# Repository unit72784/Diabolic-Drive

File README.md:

# Diabolic Drive

# 💀 The final Diabolic Drive firmware is live — locked, loaded, and lethal.This isn’t just an update — it’s a full-scale upgrade built for offensive ops in the real world. Designed by UNIT 72784. One mind. Full control. For every hacker. You’ve waited long enough. Flash it. Wreck everything. Break what must be broken. 💀
# [New firmware installation instructions are here.](https://github.com/unit72784/Diabolic-Drive/blob/main/New%20firmware%20installation%20instructions.md)
<p align="center">
  <a href="https://www.youtube.com/watch?v=nSBRwmqkTx8">
    
    <br>
    <b>Watch Diabolic Drive Teaser</b>
  </a>
</p>

---

* [Firmware ChangeLog](#firmware-changelog)
* [Usage](#usage)
* [About](#about)
* [Why Diabolic Drive ?](#why-diabolic-drive-)
* [How Stealth can Diabolic Drive go ?](#how-stealth-can-diabolic-drive-go-)
* [Features](#features)
* [Flash Software](#flash-software)
  + [Flash Atmega32u4](#flash-atmega32u4)
  + [Flash ESP8266](#flash-esp8266)
* [Programming Options](#programming-options)
  + [ESP8266](#esp8266)
  + [ATMEGA32U4](#atmega32u4)
  + [Access ATMEGA32U4 Bootloader](#access-atmega32u4-bootloader)
* [Technical Specifications](#technical-specifications)
* [Credits](#credits)

<h1>:bangbang: Diabolic Drive default access point credentials are:
  <br>Wi-Fi SSID: DDv1</br>
  Password: diabolic_drive 
  :bangbang:
</h1>

# Firmware ChangeLog 
### 1. Dynamic Hardware ID Spoofing :
Spoof the VID and PID of your Diabolic Drive over the Web UI using the USBID command.

### 2. Side-Channel Exfiltration with Keystroke Reflection
Capture and reflect keystrokes in real-time for stealthy data extraction.

### 3. LangIgnore Mode
No layout? No problem. Payloads are delivered consistently using ALT + numpad ASCII codes, bypassing language settings across all keyboard layouts.

### 4. OS Detection
Automatically detects the target operating system so you can adapt payloads accordingly.

### 5. Configurable Random Typing Cadence
Human-like keystroke timing to avoid behavioral detection systems.

### 6. Revamped Web UI
Completely refreshed interface — cleaner, faster, and more intuitive than ever.

### 7. DNS Redirection with Captive Portal
ensures all requests go to the onboard web server, displaying a captive portal instead of a “no internet” message. On mobile devices, it eliminates the need to disable mobile data to access the web interface.

### 8. Stability & Performance
Tons of under-the-hood bug fixes, stability improvements, and overall performance boosts.

## Usage
1. Plug in your Diabolic Drive
2. <b>Connect to the WiFi network `DDv1` with the default password `diabolic_drive`</b>
3. Open the browser on the device you used to connect to your Diabolic Drive and visit `192.168.4.1` or `diabolic.drive`
4. Your Diabolic Drive comes preloaded with a test Ducky script, which I used in the testing phase to check if the Diabolic Drive key stroke injection works properly. No worries about it; it's just a powershell command that retrieves the credentials of the Diabolic Drive access point from your Windows machine if it's already saved and you have connected to it from your computer before.
5. To access `Settings` along with other menus, click on the 3 horizontal bars icon (top right corner).

<h3> <del>
‼️The software that comes preloaded with the already-shipped Diabolic Drive is in a very early beta phase (built on WiFiDuck) with some modifications to suit the Diabolic Drive and to integrate the Spectre POC feature just to get things up and running. After ensuring all Diabolic Drives are delivered to the backers, I will start working on the software side and adding features to it.‼️
</del>
  <br>
  <br>
✅ <strong>This is now complete. Final firmware is released.</strong>
  
<br>Feel free to subscribe to the <a href="https://www.youtube.com/@unit72784">UNIT 72784 YouTube channel</a>; many great videos, feature updates and use-case scenarios will be posted there very soon!</br>
</h3> 

## About

Diabolic Drive isn’t just another HID injector — it’s a full-blown offensive implant wrapped in the body of a perfectly normal 64GB flash drive.

Plug it in and it plays the part: real storage, clean profile, zero suspicion. But behind the scenes, it’s wirelessly waiting to strike — injecting keystrokes, executing payloads, and slipping past defenses in plain sight.

Built for red teamers, crafted for covert ops, and born for social engineering. This isn’t a bad USB — it’s the next generation.

---

## Why Diabolic Drive ?
What’s the one USB device people still trust enough to plug in without thinking? A flash drive. No cables. No adapters. Just something simple, familiar, and everywhere.

Think about it — when was the last time you plugged in a USB cable just for data? Now think about how often flash drives get used. Exactly.

But just looking like a flash drive isn’t enough anymore — people are catching on. So Diabolic Drive doesn’t just look legit — it is legit. A full 64GB of real, usable storage. No gimmicks. No dead shells. Plug it in, and it behaves exactly like a standard thumb drive.

That’s what makes it dangerous.

It blends in, earns trust, and delivers payloads with surgical precision. Whether you’re baiting targets in the wild or slipping it into a physical pentest, Diabolic Drive is built for the job — engineered for social engineering.

***Diabolic Drive on the left, standard flash drive on the right**

## How Stealth can Diabolic Drive go ?
**there are 4 main features that make Diabolic Drive very Stealth**
- **PCB design is in Universal Flash Drive PCB shape.** For any person with good security awareness, plugging in a generic-looking or very old-fashioned USB 2.0 flash drive might not be the best option to go for., This is why I decided to go with the trendy shapes of modern-looking USB 3.0 flash drives and the most common available models. I did lots of recon, got many models disassembled, identified the PCB dimensions, and finally managed to get a universal PCB shape that I needed to design my PCB identical to to help the Diabolic Drive be much more stealthy, hiding itself in many common USB 3.0 flash drive enclosures out there!
 **Disclaimer :  Enclosure in image below is for demonstration purposes only !**

- **plug in your Diabolic Drive to a USB port will raise only one USB plug in sound** When Diabolic Drive is plugged into a host computer, it acts just like a regular USB flash drive, including any audio notifications you would normally hear when plugging in a new USB device. Your computer will identify Diabolic Drive as a flash drive, HID device, and virtual COM port simultaneously <b>(Now with SPECTRE, your computer will only identify it as a flash drive, and the HID interface remains dormant until you fire your payload.)</b>, but will only trigger an audio notification once, which is how a standard drive would behave. 
<p align="center">
  <a href="https://www.youtube.com/watch?v=JKw52I0WJpA">
    
    <br>
    <b>Watch Diabolic Drive Stealthy Feature Demo</b>
  </a>
</p>

- **Hardware IDs are spoofable.** Diabolic Drive Flash storage hardware IDs can be spoofed for maximum stealthiness. These IDs include VID, PID, Vendor info, Product info, Rev info, Vendor string, Product String, and SN. This makes distinguishing Diabolic Drive very difficult!
<p align="center">
  <a href="https://www.youtube.com/watch?v=iDItm9KI_z4">
    
    <br>
    <b>Watch Diabolic Drive in "Stealth mode," with spoofed hardware IDs </b>
  </a>
</p>

**Have a look at the image below. Can you spot which one is Diabolic Drive?**

- a **stealth mode** that can be preprogrammed and makes your computer read the ATMEGA32U4 as a HID device only, hiding its identity of running an Arduino Bootloader and its COM port from the Windows device manager, which enhances Diabolic Drive's covert usability.
- the **Spectre status**, which you can learn more about  [here](https://www.crowdsupply.com/unit-72784/diabolic-drive/updates/introducing-spectre-our-latest-stealth-feature).

## Features
Diabolic Drive runs on humble, battle-tested hardware — but don’t let that fool you.
It’s been pushed to its absolute limits with stealth, control, and adaptability in mind.
Designed to give you full flexibility, total control, and future-proof expansion, all without sacrificing speed or stealth.
### ✅ Features Ready (Out of the Box)

- **Dual Communication (Serial + I²C)**  
  ATMEGA32U4 and ESP8266 are wired over both Serial *and* I²C, making it compatible with nearly every open-source firmware built for these two chips.  
  > Supports: `WiFi Duck`, `WiFi Ducky`, `ESPloitV2`, `WHID`, `supremeDuck`, and more.

- **Payloads + Storage — Simultaneously**  
  Fire off keystrokes *and* read/write real data at the same time.  
  Full 64GB flash storage is usable even while executing wireless payloads.

- **Web-Based Control Interface**  
  No apps, no drivers. Just connect over Wi-Fi and command everything from a clean, mobile-friendly Web UI.

- **Hardware ID Cloning**  
  Clone the ATMEGA32U4 and Flash storage hardware IDs (VID, PID, etc.) for stealth.  
  > ~~*Note: not supported live/on-the-fly — but fully programmable.*~~ **Now Dynamic Hardware ID Spoofing works over the Web UI using the USBID command.**

## Flash Software

<b> I know I'm very bad at explaining things, but I will ensure I make a series of Youtube videos for a better explanation of how this process works very soon. :)
Also, feel free to do yours, and I will put your links here.:) </b> 

## See Here : [New firmware installation instructions](https://github.com/unit72784/Diabolic-Drive/blob/main/New%20firmware%20installation%20instructions.md)

### Flash ATmega32U4

If your Diabolic Drive is still running the beta firmware it shipped with, you'll need to:

1. Connect to the device over Wi-Fi.
2. Press the **Start** button in the Web UI to expose the ATmega32U4 to your computer.

> ⚠️ By default, the ATmega32U4 is dormant due to **SPECTRE** mode.

**Do not** enable *Diabolic Drive Stealth Mode* unless you have either:
- a **Diabolic Drive Programmer**, or  
- an **Arduino Pro Micro** configured as an ISP.

Otherwise, you'll lose the ability to upload sketches to the ATmega32U4.

---

### Flash ESP8266

To flash the ESP8266:

1. Ensure the ATmega32U4 is exposed and shows up as a **COM port** in Windows Device Manager.
2. Upload [the provided sketch](https://github.com/unit72784/Diabolic-Drive/blob/main/ESP8266_Programmer_via_ATMEGA32U4/ESP8266_Programmer_via_ATMEGA32U4.ino) to the ATmega32U4.
3. Once the upload completes successfully, the Diabolic Drive Wi-Fi will disappear — indicating that the ESP has entered **flashing mode**.

## Programming Options

### ESP8266
   + OTA ( Over The Air ) through its web interface
   + through ATMEGA32U4 acting as a Serial Bridge giving you full control over it in case something went wrong (also supports NodeMCU Firmware Programmer App )
### ATMEGA32U4
   + Uploading Arduino Sketches : by directly plug your Diabolic Drive into the computer as ATMEGA32U4 has native USB support through USB transceiver built into it that handles the USB connection .
### Access ATMEGA32U4 Bootloader
   + This is a unique way by UNIT 72784 that gives you full control over the ATMEGA32U4 of a Diabolic Drive by accessing its boatloader through USB 3.0 defined pins. .. Diabolic Drive uses a modified version of the Arduino Leonardo bootloader by default and is also compatible with the original Arduino Leonardo bootloader.
<p align="center">
  <a href="https://www.youtube.com/watch?v=L3nXUaHzDiY">
    
    <br>
    <b>Watch the POC Demo</b>
  </a>
</p>

## Technical Specifications
- ATMEGA32U4 running at 16MHz and 5V .
- ESP8266ex running at 160MHZ at 3.3v with onboard LDO Regulator .
- ESP8266ex has 4MB of memory able to store millions of characters to save your payloads .
- High gain 4.1dBi ceramic chip 2.4G Wireless antenna.
- 64GB Flash Storage with average reading and writing speed of 20MB/s , 10MB/s respectively. Demo available [here](https://www.youtube.com/watch?v=Hp0QsIaciWE)

## Credits
###  on the Software Side
- [WiFiDuck](https://github.com/SpacehuhnTech/WiFiDuck) A huge thanks! 
- [supremeDuck](https://github.com/michalmonday/supremeDuck) the most feature-rich one! Actually, I like how creative Michal Borowski is!
### on the Hardware Side
- [HAK5](https://github.com/hak5darren/) If Rubber Ducky didn't exist, then Diabolic Drive would never exist! Actually, Darren is a godfather for all of these tools!
- [Mike Grover](https://twitter.com/_MG_) miniaturization inspiration!
### on the media, funding distribution side 
[CrowdSupply](https://www.crowdsupply.com/) They are the best crowdfunding site and the best team! :heart:

This is my first repo, so I'm not familiar with this staff, feel free to start a pull request for adding credits for anyone you believe was a part of this project. :)

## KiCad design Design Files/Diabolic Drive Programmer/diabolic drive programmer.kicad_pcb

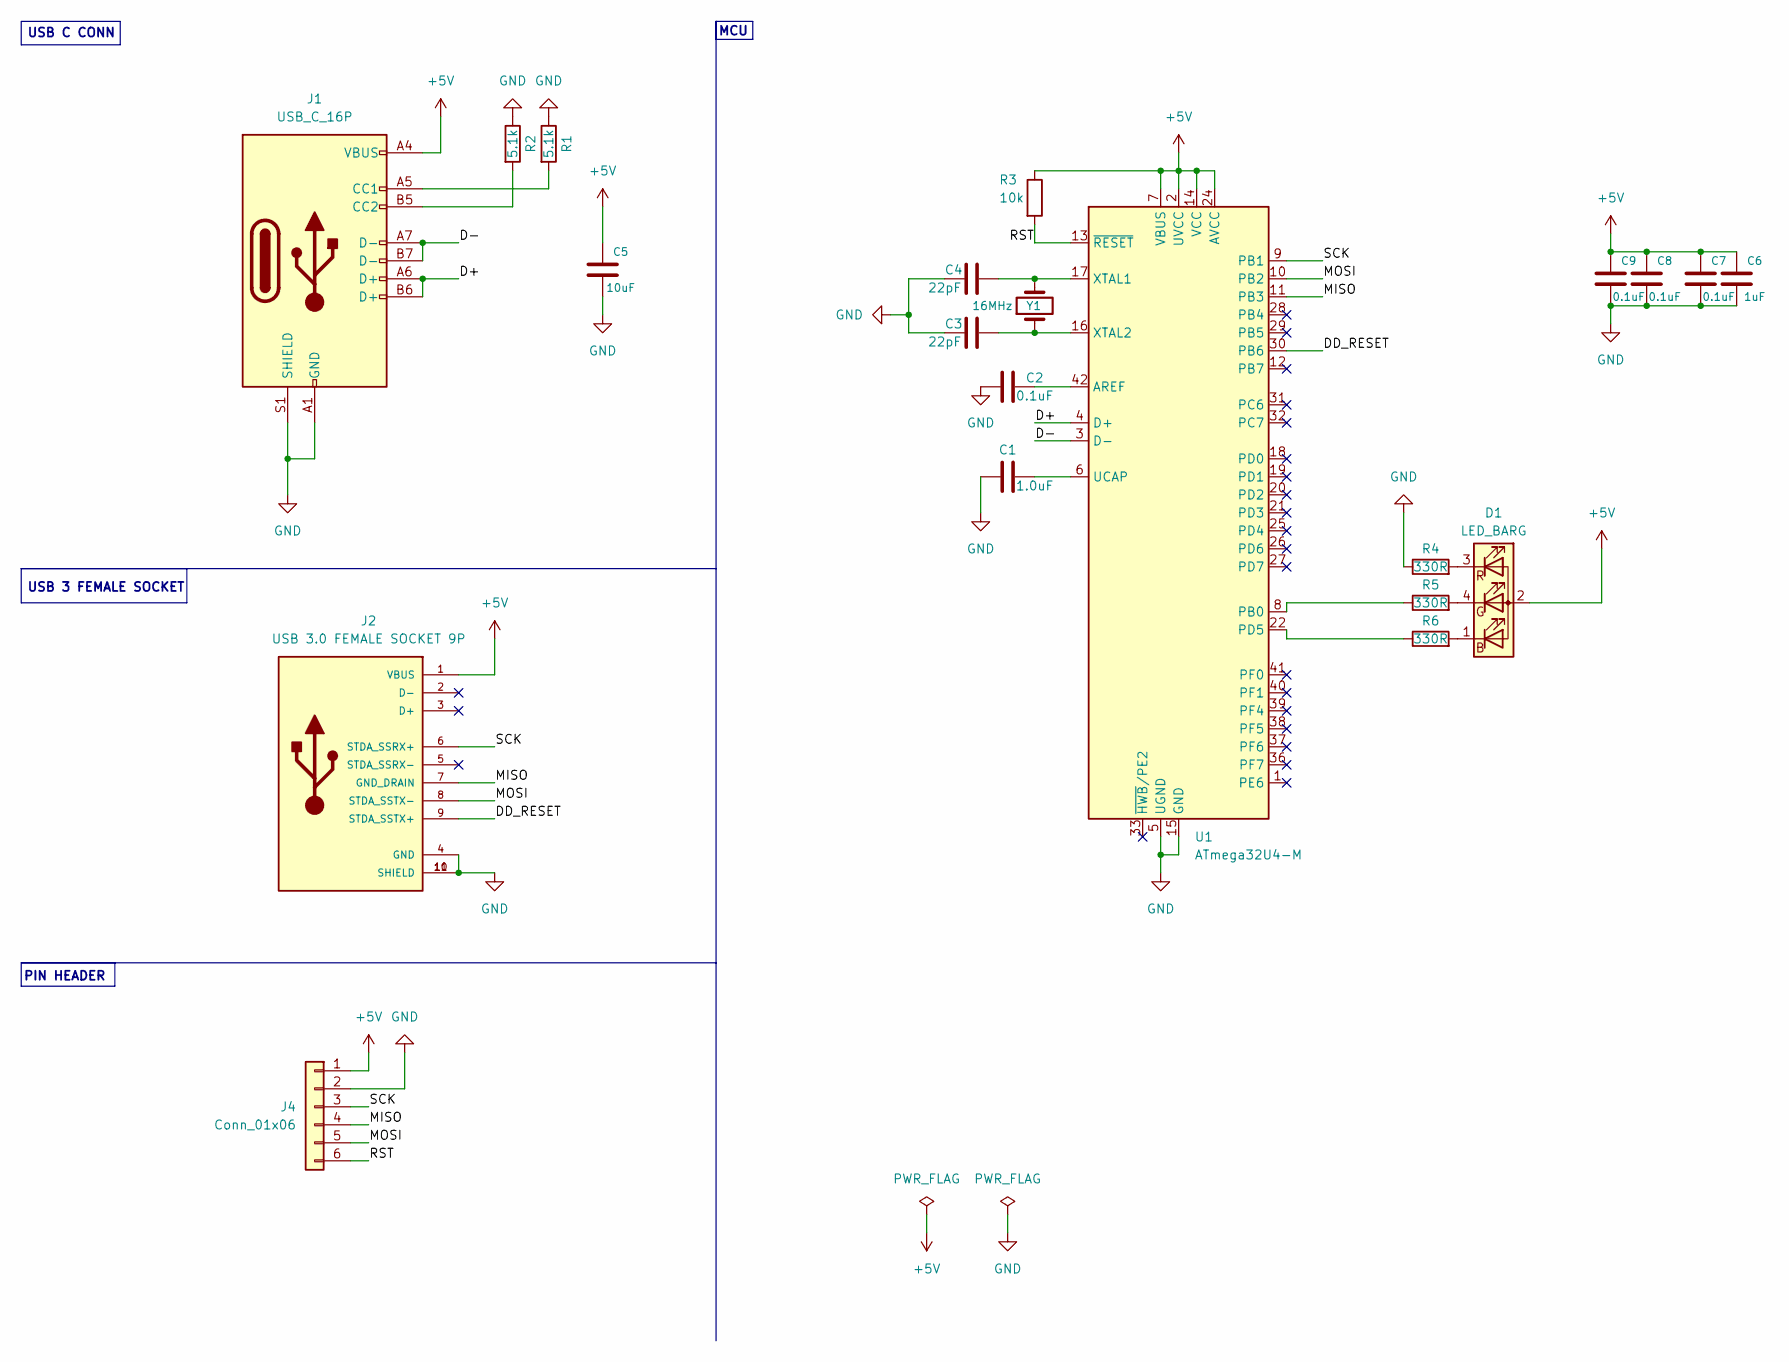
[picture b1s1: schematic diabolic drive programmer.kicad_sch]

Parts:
C1: 1.0uF; C_0603_1608Metric
C2, C7, C8, C9: 0.1uF; C_0603_1608Metric
C3, C4: 22pF; C_0603_1608Metric
C5: 10uF; C_0603_1608Metric
C6: 1uF; C_0603_1608Metric
D1: LED_BARG; LED_Kingbright_APFA3010_3x1.5mm_Horizontal
J1: USB_C_16P; USB_C_Receptacle_GCT_USB4105-xx-A_16P_TopMnt_Horizontal
J2: USB 3.0 FEMALE SOCKET 9P; GCT_USB1075-XX-X-X_REVE
J4: Conn_01x06; PinHeader_1x06_P2.54mm_Vertical
R1, R2: 5.1k; R_0603_1608Metric
R3: 10k; R_0603_1608Metric
R4, R5, R6: 330R; R_0603_1608Metric
U1: ATmega32U4-M; QFN-44-1EP_7x7mm_P0.5mm_EP5.2x5.2mm
Y1: 16MHz; Crystal_SMD_5032-4Pin_5.0x3.2mm

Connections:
+5V: C5.2, C6.2, C7.2, C8.2, C9.2, D1.2 (A), J1.A4 (VBUS), J1.A9 (VBUS), J1.B4 (VBUS), J1.B9 (VBUS), J2.1 (VBUS), J4.1, R3.1, U1.2 (UVCC), U1.7 (VBUS), U1.14 (VCC), U1.24 (AVCC), U1.34 (VCC), U1.44 (AVCC)
/D+: J1.A6 (D+), J1.B6 (D+), U1.4 (D+)
/D-: J1.A7 (D-), J1.B7 (D-), U1.3 (D-)
/DD_RESET: J2.9 (STDA_SSTX+), U1.30 (PB6)
/MISO: J2.7 (GND_DRAIN), J4.4, U1.11 (PB3)
/MOSI: J2.8 (STDA_SSTX-), J4.5, U1.10 (PB2)
/RST: J4.6, R3.2, U1.13 (~RESET)
/SCK: J2.6 (STDA_SSRX+), J4.3, U1.9 (PB1)
GND: C1.1, C2.1, C3.1, C4.1, C5.1, C6.1, C7.1, C8.1, C9.1, J1.A1 (GND), J1.A12 (GND), J1.B1 (GND), J1.B12 (GND), J1.S1 (SHIELD), J2.4 (GND), J2.10 (SHIELD), J2.11 (SHIELD), J4.2, R1.1, R2.1, R4.1, U1.5 (UGND), U1.15 (GND), U1.23 (GND), U1.35 (GND), U1.43 (GND), U1.45 (GND), Y1.2, Y1.4
unnamed: D1.1 (BK), R6.2
unnamed: D1.4 (GK), R5.2
unnamed: D1.3 (RK), R4.2
unnamed: J1.A5 (CC1), R1.2
unnamed: J1.B5 (CC2), R2.2
unnamed: C2.2, U1.42 (AREF)
unnamed: R5.1, U1.8 (PB0)
unnamed: R6.1, U1.22 (PD5)
unnamed: C1.2, U1.6 (UCAP)
unnamed: C4.2, U1.17 (XTAL1), Y1.3
unnamed: C3.2, U1.16 (XTAL2), Y1.1

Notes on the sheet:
USB C CONN
MCU
USB 3 FEMALE SOCKET
PIN HEADER

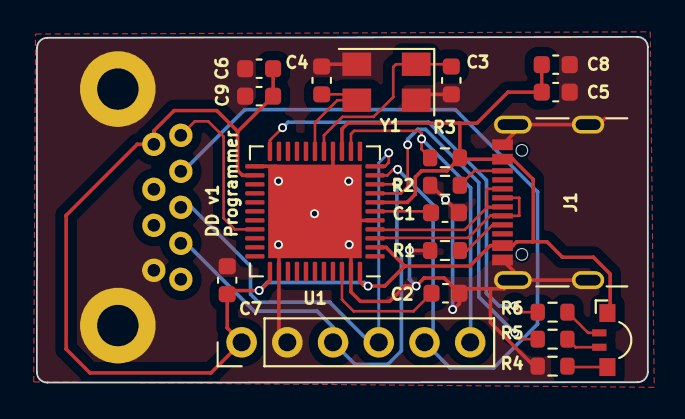
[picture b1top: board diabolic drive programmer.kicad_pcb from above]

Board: 2 copper layers, 33.9 x 19.2 mm, 21 parts (0 on the bottom side), 20 nets.

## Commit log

2023-04-19 Update ESP8266 through ATMEGA32U4
2023-05-14 img folder uploaded , README.md updated
2023-07-02 new images uploaded
2023-07-19 Custom 3D printed enclosure files upload
2023-12-05 Diabolic Drive final layout images upload
2024-01-13 Design Files Uploaded
2024-01-13 Custom Board JSON file Uploaded
2024-01-13 Flashing Instructions Added!
2024-01-20 schematic updated to reflect the latest board of the already shipped diabolic drives.
2025-05-30 New Firmware Announcement
2025-05-30 ATmega Flasher files uploaded!
